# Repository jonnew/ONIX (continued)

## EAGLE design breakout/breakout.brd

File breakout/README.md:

:warning: This project has moved to a dedicated repository: https://github.com/open-ephys/onix-breakout
This folder should be considered archived.

# ONIX Breakout Board
This board allows bench access to the IO provided by the
[fmc-host board](../fmc-host/README.md). It features:

- 4x headstage ports, each with a power switch
- 3x, passive, high-seed clock feed throughs
- BNC, IDC (ribbon), or direct wire access to 12 analog inputs or outputs
- IDC (ribbon) or direct wire access to 8 digital outputs and 8 digital inpouts
- 6 buttons for marking experimental events
- 41 state-indication LEDs
- Full-speed, USB 2.0 access to the onboard [TinyFPGA
  BX](https://www.crowdsupply.com/tinyfpga/tinyfpga-bx) for communication,
  programming, and customization 
- HARP bus
- Rugged M6 or 1/4-20 mounting options compliant with 19" racks and optical
  tables
- Fully open-source gateware and use of fully open-source FPGA toolchain (yosys
  & nextpnr)

## Documentation
Documentation can be found
[here](https://open-ephys.github.io/onix-docs/Hardware%20Guide/Breakout%20Boards/breakout_1r4.html)

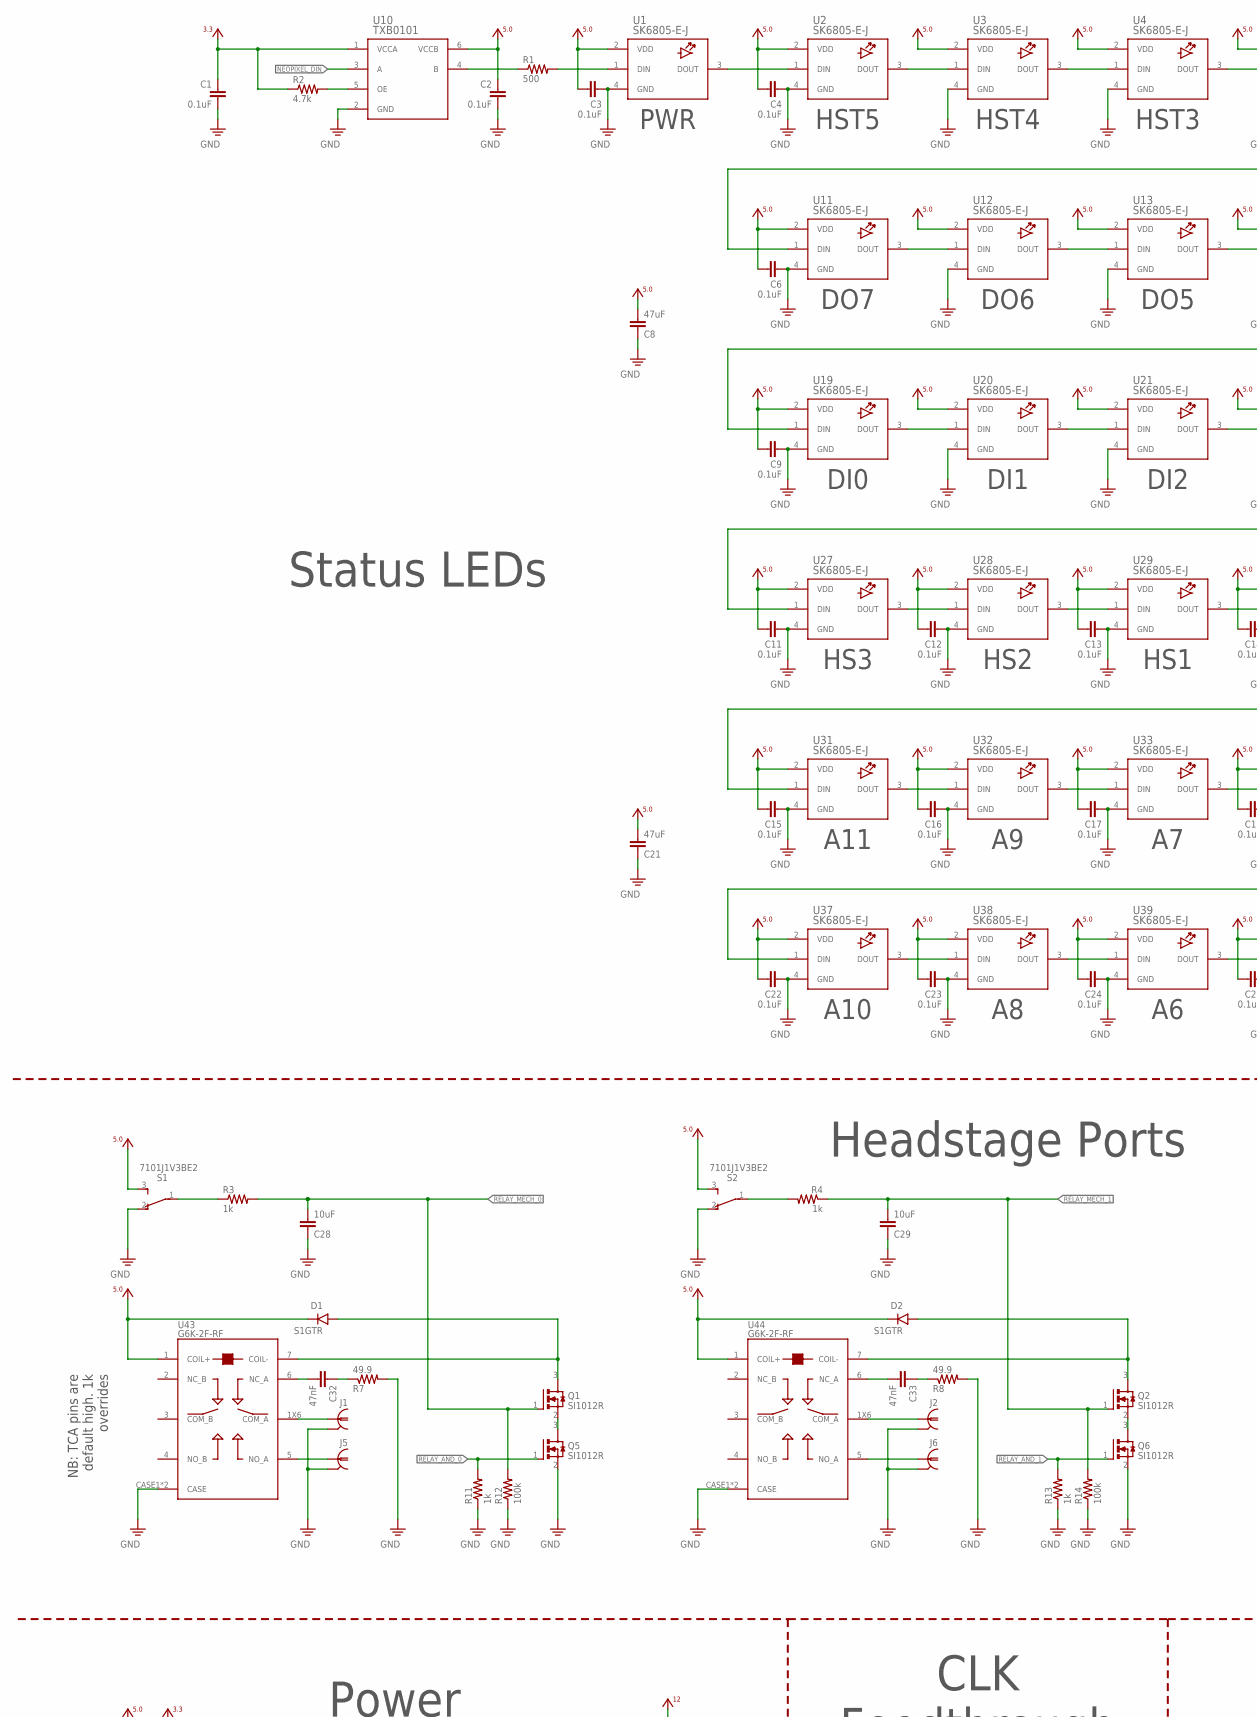
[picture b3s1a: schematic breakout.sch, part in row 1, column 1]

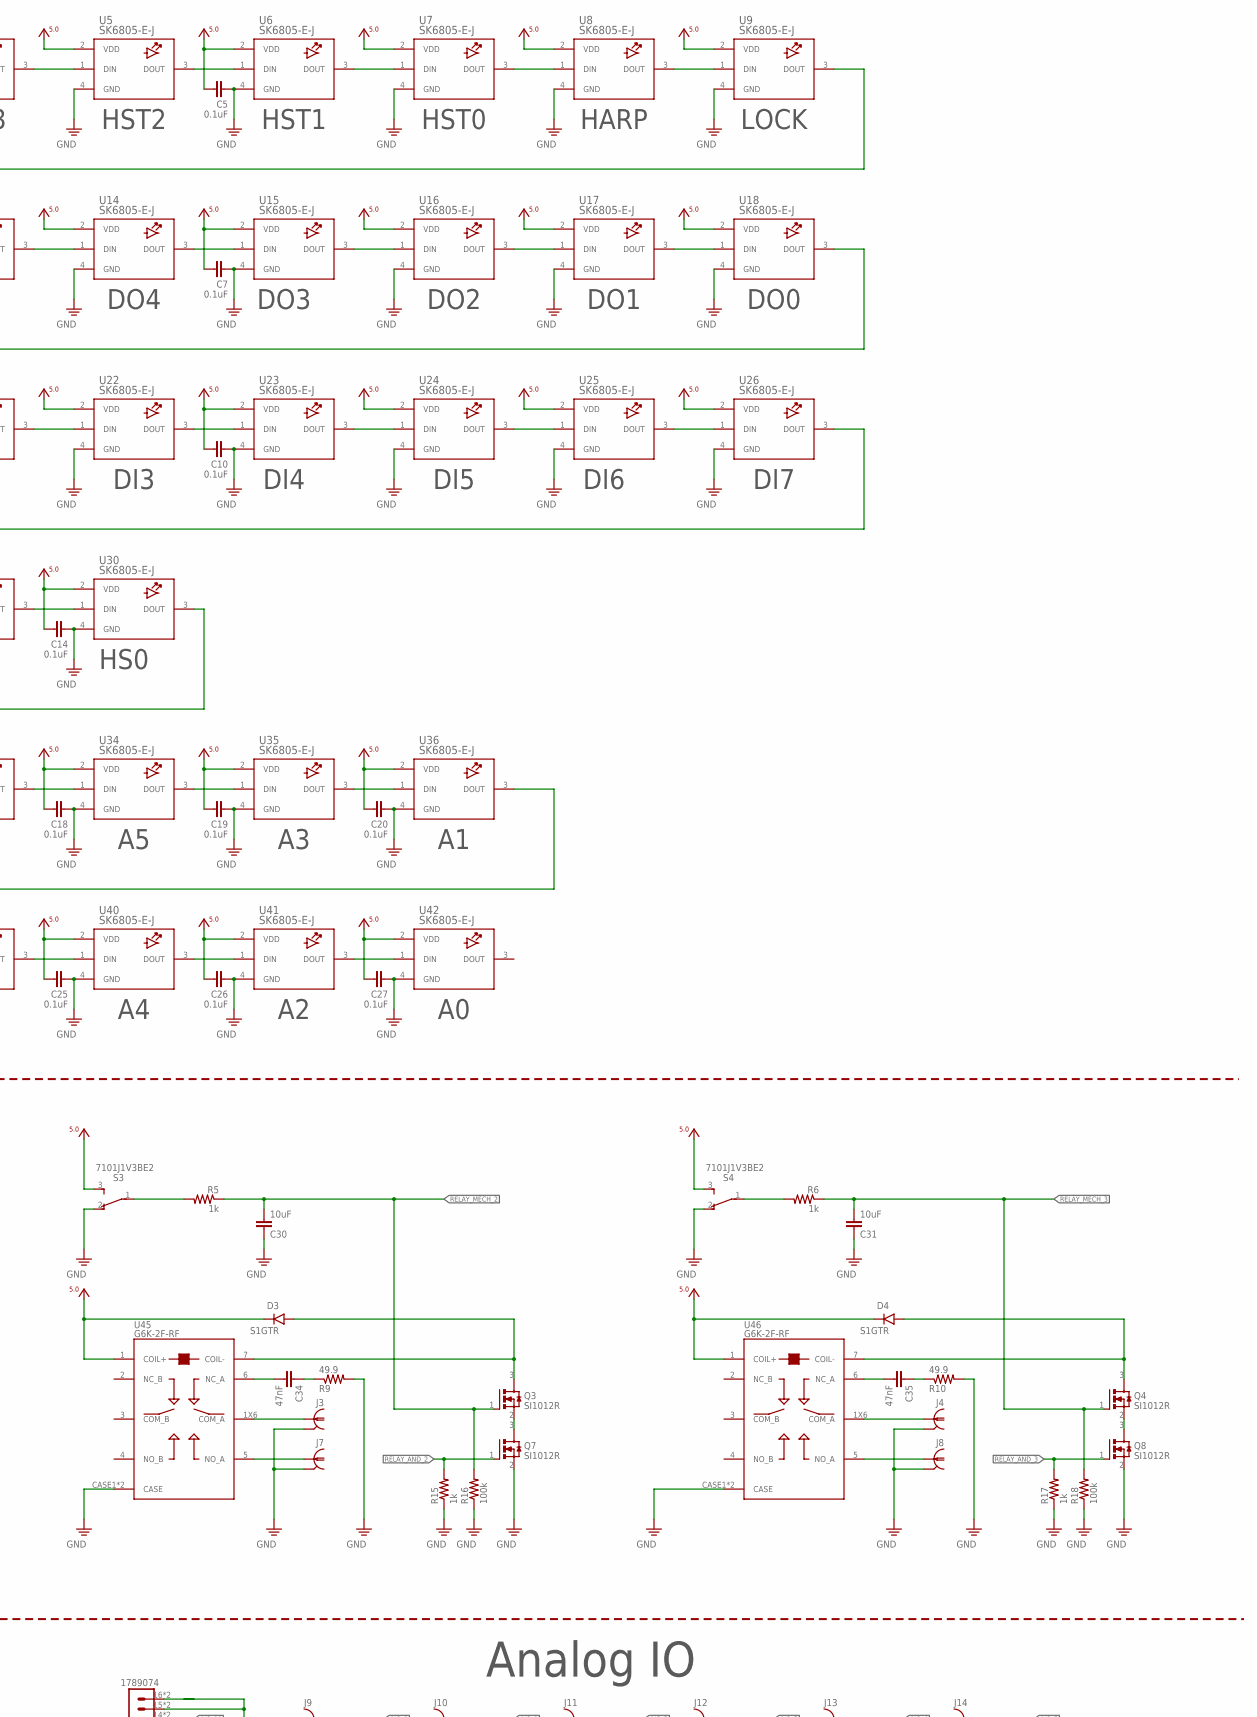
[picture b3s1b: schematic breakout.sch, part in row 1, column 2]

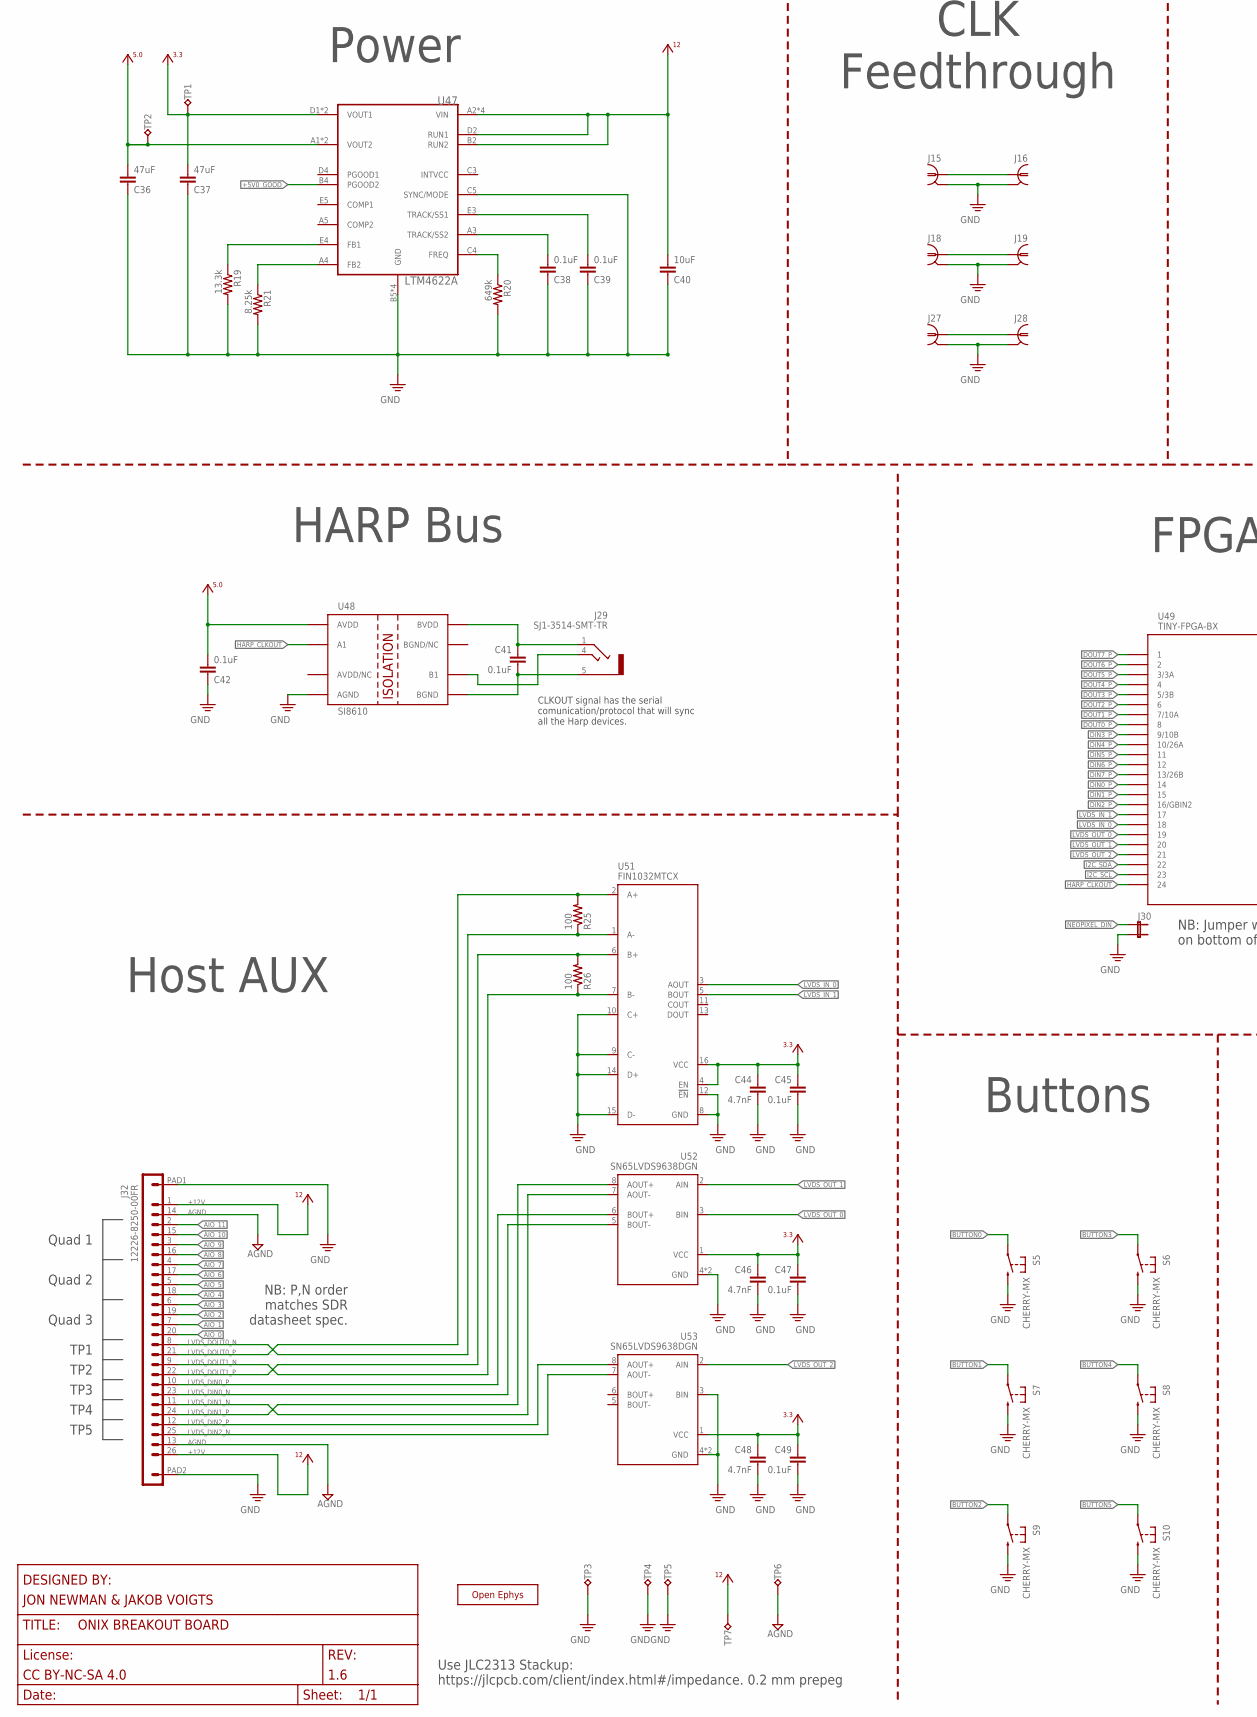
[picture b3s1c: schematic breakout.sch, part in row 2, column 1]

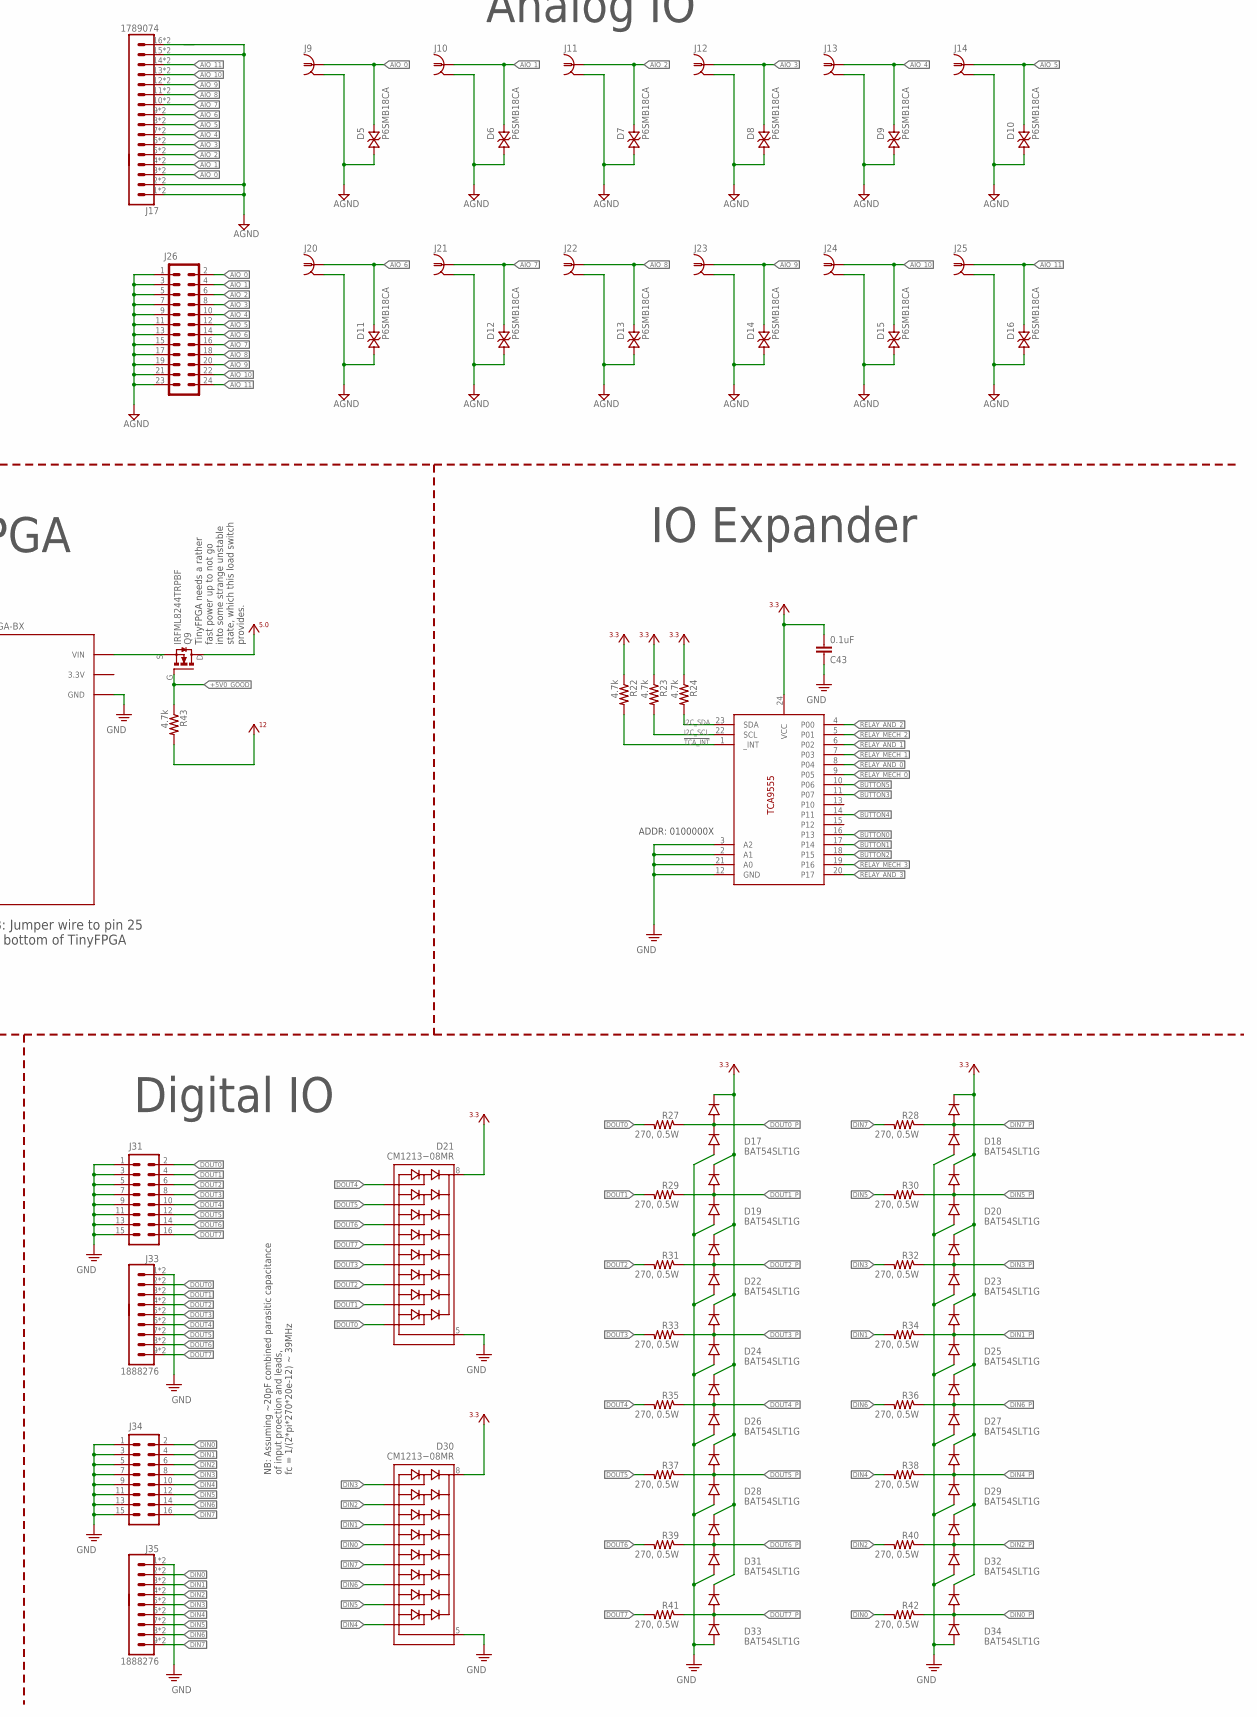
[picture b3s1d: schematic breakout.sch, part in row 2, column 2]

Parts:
C1, C2, C3, C4, C5, C6, C7, C9, C10, C11, C12, C13, C14, C15, C16, C17, C18, C19, C20, C22, C23, C24, C25, C26, C27, C38, C39, C41, C42, C43, C45, C47, C49: 0.1uF; 0402
C8, C21, C36, C37: 47uF; 1210
C28, C29, C30, C31, C40: 10uF; 0805
C32, C33, C34, C35: 47nF; 0402
C44, C46, C48: 4.7nF; 0402
D1, D2, D3, D4: S1GTR; SMA-DO214AC
D5, D6, D7, D8, D9, D10, D11, D12, D13, D14, D15, D16: P6SMB18CA; SMA-DO214AC
D17, D18, D19, D20, D22, D23, D24, D25, D26, D27, D28, D29, D31, D32, D33, D34: BAT54SLT1G; SOT23
D21, D30: CM1213−08MR; MSOP-10-3X3
J1, J2, J3, J4, J16, J19, J28: COAX_SMA-VERT; SMA_JACK_142-0701-201
J5, J6, J7, J8, J15, J18, J27: COAX_MMCX-THRU; MMCX-THRU
J9, J10, J11, J12, J13, J14, J20, J21, J22, J23, J24, J25: COAX_0731010360; 0731010360
J17: 1789074; SCREW16-2
J26: 69168-124HLF; 2X12-BIG
J29: SJ1-3514-SMT-TR; 35RASMT2BHNTRX
J30: JP2E_THRU-HOLE; JP2
J31, J34: 69168-116HLF; 2X08-BIG
J32: 12226-8250-00FR; 12226-82X0-00XX
J33, J35: 1888276; SCREW9-2
Q1, Q2, Q3, Q4, Q5, Q6, Q7, Q8: SI1012R; SC75
Q9: IRFML8244TRPBF; SOT23-GSD
R1: 500; 0402
R2, R22, R23, R24, R43: 4.7k; 0402
R3, R4, R5, R6, R11, R13, R15, R17: 1k; 0402
R7, R8, R9, R10: 49.9; 0402
R12, R14, R16, R18: 100k; 0402
R19: 13.3k; 0402
R20: 649k; 0402
R21: 8.25k; 0402
R25, R26: 100; 0402
R27, R28, R29, R30, R31, R32, R33, R34, R35, R36, R37, R38, R39, R40, R41, R42: 270, 0.5W; 0805
S1, S2, S3, S4: 7101J1V3BE2; CK_7101J1V3QE2
S5, S6, S7, S8, S9, S10: CHERRY-MX
TP1, TP2: TPTP19R; TP19R
TP3, TP4, TP5, TP6, TP7: TP_2MM; TESTPOINT_2MM
U1, U2, U3, U4, U5, U6, U7, U8, U9, U11, U12, U13, U14, U15, U16, U17, U18, U19, U20, U21, U22, U23, U24, U25, U26, U27, U28, U29, U30, U31, U32, U33, U34, U35, U36, U37, U38, U39, U40, U41, U42: SK6805-E-J; NEOPIXEL-1.5X1.5
U10: TXB0101; SOT23-6
U43, U44, U45, U46: G6K-2F-RF; G6KU-2F-RF
U47: LTM4622A; BGA_5X5_625X625
U48: SI8610; SO-08
U49: TINY-FPGA-BX; TINY-FPGA-BX_BASIC
U50: TCA9555; TSSOP-24
U51: FIN1032MTCX; TSSOP-16
U52, U53: SN65LVDS9638DGN; MSOP-8-PAD-3X3
X: OE-LOGO_28X20; OE-LOGO-28X20

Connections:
!TCA_INT: R22.2, U50.1 (_INT)
+3V3: C1.1, C37.2, C43.2, C44.1, C45.1, C46.1, C47.1, C48.1, C49.1, D17.2 (C), D18.2 (C), D19.2 (C), D20.2 (C), D21.8 (VCC), D22.2 (C), D23.2 (C), D24.2 (C), D25.2 (C), D26.2 (C), D27.2 (C), D28.2 (C), D29.2 (C), D30.8 (VCC), D31.2 (C), D32.2 (C), D33.2 (C), D34.2 (C), R2.1, R22.1, R23.1, R24.1, TP1.TP, U10.1 (VCCA), U47.D1 (VOUT1), U47.E1 (VOUT1), U50.24 (VCC), U51.4 (EN), U51.16 (VCC), U52.1 (VCC), U53.1 (VCC)
+5V0: C2.1, C3.2, C4.2, C5.2, C6.2, C7.2, C8.2, C9.2, C10.2, C11.2, C12.2, C13.2, C14.2, C15.2, C16.2, C17.2, C18.2, C19.2, C20.2, C21.2, C22.2, C23.2, C24.2, C25.2, C26.2, C27.2, C36.2, C42.2, D1.C, D2.C, D3.C, D4.C, Q9.D, S1.3, S2.3, S3.3, S4.3, TP2.TP, U1.2 (VDD), U2.2 (VDD), U3.2 (VDD), U4.2 (VDD), U5.2 (VDD), U6.2 (VDD), U7.2 (VDD), U8.2 (VDD), U9.2 (VDD), U10.6 (VCCB), U11.2 (VDD), U12.2 (VDD), U13.2 (VDD), U14.2 (VDD), U15.2 (VDD), U16.2 (VDD), U17.2 (VDD), U18.2 (VDD), U19.2 (VDD), U20.2 (VDD), U21.2 (VDD), U22.2 (VDD), U23.2 (VDD), U24.2 (VDD), U25.2 (VDD), U26.2 (VDD), U27.2 (VDD), U28.2 (VDD), U29.2 (VDD), U30.2 (VDD), U31.2 (VDD), U32.2 (VDD), U33.2 (VDD), U34.2 (VDD), U35.2 (VDD), U36.2 (VDD), U37.2 (VDD), U38.2 (VDD), U39.2 (VDD), U40.2 (VDD), U41.2 (VDD), U42.2 (VDD), U43.1 (COIL+), U44.1 (COIL+), U45.1 (COIL+), U46.1 (COIL+), U47.A1 (VOUT2), U47.B1 (VOUT2), U48.1 (AVDD)
+5V0_GOOD: Q9.G, R43.1, U47.B4 (PGOOD2)
+12V: C40.2, J32.1, J32.26, R43.2, TP7.1, U47.A2 (VIN), U47.B2 (RUN2), U47.B3 (VIN), U47.D2 (RUN1), U47.D3 (VIN), U47.E2 (VIN)
AGND: D5.A (1), D6.A (1), D7.A (1), D8.A (1), D9.A (1), D10.A (1), D11.A (1), D12.A (1), D13.A (1), D14.A (1), D15.A (1), D16.A (1), J9.2, J9.3 (2), J9.4 (2), J9.5 (2), J10.2, J10.3 (2), J10.4 (2), J10.5 (2), J11.2, J11.3 (2), J11.4 (2), J11.5 (2), J12.2, J12.3 (2), J12.4 (2), J12.5 (2), J13.2, J13.3 (2), J13.4 (2), J13.5 (2), J14.2, J14.3 (2), J14.4 (2), J14.5 (2), J17.1, J17.2, J17.15, J17.16, J17.17 (1), J17.18 (2), J17.31 (15), J17.32 (16), J20.2, J20.3 (2), J20.4 (2), J20.5 (2), J21.2, J21.3 (2), J21.4 (2), J21.5 (2), J22.2, J22.3 (2), J22.4 (2), J22.5 (2), J23.2, J23.3 (2), J23.4 (2), J23.5 (2), J24.2, J24.3 (2), J24.4 (2), J24.5 (2), J25.2, J25.3 (2), J25.4 (2), J25.5 (2), J26.1, J26.3, J26.5, J26.7, J26.9, J26.11, J26.13, J26.15, J26.17, J26.19, J26.21, J26.23, J32.13, J32.14, TP6.1
AIO_0: D5.C (2), J9.1, J17.3, J17.19 (3), J26.2, J32.20
AIO_1: D6.C (2), J10.1, J17.4, J17.20 (4), J26.4, J32.7
AIO_2: D7.C (2), J11.1, J17.5, J17.21 (5), J26.6, J32.19
AIO_3: D8.C (2), J12.1, J17.6, J17.22 (6), J26.8, J32.6
AIO_4: D9.C (2), J13.1, J17.7, J17.23 (7), J26.10, J32.18
AIO_5: D10.C (2), J14.1, J17.8, J17.24 (8), J26.12, J32.5
AIO_6: D11.C (2), J17.9, J17.25 (9), J20.1, J26.14, J32.17
AIO_7: D12.C (2), J17.10, J17.26 (10), J21.1, J26.16, J32.4
AIO_8: D13.C (2), J17.11, J17.27 (11), J22.1, J26.18, J32.16
AIO_9: D14.C (2), J17.12, J17.28 (12), J23.1, J26.20, J32.3
AIO_10: D15.C (2), J17.13, J17.29 (13), J24.1, J26.22, J32.15
AIO_11: D16.C (2), J17.14, J17.30 (14), J25.1, J26.24, J32.2
BUTTON0: S5.SW1, U50.16 (P13)
BUTTON1: S7.SW1, U50.17 (P14)
BUTTON2: S9.SW1, U50.18 (P15)
BUTTON3: S6.SW1, U50.11 (P07)
BUTTON4: S8.SW1, U50.14 (P11)
BUTTON5: S10.SW1, U50.10 (P06)
DIN0: D30.4 (CH4), J34.2, J35.2, J35.11 (2), R42.2
DIN0_P: D34.3 (COMM), R42.1, U49.14
DIN1: D30.3 (CH3), J34.4, J35.3, J35.12 (3), R34.2
DIN1_P: D25.3 (COMM), R34.1, U49.15
DIN2: D30.2 (CH2), J34.6, J35.4, J35.13 (4), R40.2
DIN2_P: D32.3 (COMM), R40.1, U49.16 (16/GBIN2)
DIN3: D30.1 (CH1), J34.8, J35.5, J35.14 (5), R32.2
DIN3_P: D23.3 (COMM), R32.1, U49.9 (9/10B)
DIN4: D30.10 (CH8), J34.10, J35.6, J35.15 (6), R38.2
DIN4_P: D29.3 (COMM), R38.1, U49.10 (10/26A)
DIN5: D30.9 (CH7), J34.12, J35.7, J35.16 (7), R30.2
DIN5_P: D20.3 (COMM), R30.1, U49.11
DIN6: D30.7 (CH6), J34.14, J35.8, J35.17 (8), R36.2
DIN6_P: D27.3 (COMM), R36.1, U49.12
DIN7: D30.6 (CH5), J34.16, J35.9, J35.18 (9), R28.2
DIN7_P: D18.3 (COMM), R28.1, U49.13 (13/26B)
DOUT0: D21.10 (CH8), J31.2, J33.2, J33.11 (2), R27.2
DOUT0_P: D17.3 (COMM), R27.1, U49.8
DOUT1: D21.9 (CH7), J31.4, J33.3, J33.12 (3), R29.2
DOUT1_P: D19.3 (COMM), R29.1, U49.7 (7/10A)
DOUT2: D21.7 (CH6), J31.6, J33.4, J33.13 (4), R31.2
DOUT2_P: D22.3 (COMM), R31.1, U49.6
DOUT3: D21.6 (CH5), J31.8, J33.5, J33.14 (5), R33.2
DOUT3_P: D24.3 (COMM), R33.1, U49.5 (5/3B)
DOUT4: D21.1 (CH1), J31.10, J33.6, J33.15 (6), R35.2
DOUT4_P: D26.3 (COMM), R35.1, U49.4
DOUT5: D21.2 (CH2), J31.12, J33.7, J33.16 (7), R37.2
DOUT5_P: D28.3 (COMM), R37.1, U49.3 (3/3A)
DOUT6: D21.3 (CH3), J31.14, J33.8, J33.17 (8), R39.2
DOUT6_P: D31.3 (COMM), R39.1, U49.2
DOUT7: D21.4 (CH4), J31.16, J33.9, J33.18 (9), R41.2
DOUT7_P: D33.3 (COMM), R41.1, U49.1
GND: C1.2, C2.2, C3.1, C4.1, C5.1, C6.1, C7.1, C8.1, C9.1, C10.1, C11.1, C12.1, C13.1, C14.1, C15.1, C16.1, C17.1, C18.1, C19.1, C20.1, C21.1, C22.1, C23.1, C24.1, C25.1, C26.1, C27.1, C28.1, C29.1, C30.1, C31.1, C36.1, C37.1, C38.1, C39.1, C40.1, C42.1, C43.1, C44.2, C45.2, C46.2, C47.2, C48.2, C49.2, D17.1 (A), D18.1 (A), D19.1 (A), D20.1 (A), D21.5 (VSS), D22.1 (A), D23.1 (A), D24.1 (A), D25.1 (A), D26.1 (A), D27.1 (A), D28.1 (A), D29.1 (A), D30.5 (VSS), D31.1 (A), D32.1 (A), D33.1 (A), D34.1 (A), J1.GND$1 (2), J1.GND$2 (2), J1.GND$3 (2), J1.GND$4 (2), J2.GND$1 (2), J2.GND$2 (2), J2.GND$3 (2), J2.GND$4 (2), J3.GND$1 (2), J3.GND$2 (2), J3.GND$3 (2), J3.GND$4 (2), J4.GND$1 (2), J4.GND$2 (2), J4.GND$3 (2), J4.GND$4 (2), J5.GND@1 (2), J5.GND@2 (2), J5.GND@3 (2), J5.GND@4 (2), J6.GND@1 (2), J6.GND@2 (2), J6.GND@3 (2), J6.GND@4 (2), J7.GND@1 (2), J7.GND@2 (2), J7.GND@3 (2), J7.GND@4 (2), J8.GND@1 (2), J8.GND@2 (2), J8.GND@3 (2), J8.GND@4 (2), J15.GND@1 (2), J15.GND@2 (2), J15.GND@3 (2), J15.GND@4 (2), J16.GND$1 (2), J16.GND$2 (2), J16.GND$3 (2), J16.GND$4 (2), J18.GND@1 (2), J18.GND@2 (2), J18.GND@3 (2), J18.GND@4 (2), J19.GND$1 (2), J19.GND$2 (2), J19.GND$3 (2), J19.GND$4 (2), J27.GND@1 (2), J27.GND@2 (2), J27.GND@3 (2), J27.GND@4 (2), J28.GND$1 (2), J28.GND$2 (2), J28.GND$3 (2), J28.GND$4 (2), J30.2, J31.1, J31.3, J31.5, J31.7, J31.9, J31.11, J31.13, J31.15, J32.PAD1, J32.PAD2, J33.1, J33.10 (1), J34.1, J34.3, J34.5, J34.7, J34.9, J34.11, J34.13, J34.15, J35.1, J35.10 (1), Q5.2 (S), Q6.2 (S), Q7.2 (S), Q8.2 (S), R7.2, R8.2, R9.2, R10.2, R11.1, R12.1, R13.1, R14.1, R15.1, R16.1, R17.1, R18.1, R19.2, R20.2, R21.2, S1.2 (1), S2.2 (1), S3.2 (1), S4.2 (1), S5.SW2 (S), S6.SW2 (S), S7.SW2 (S), S8.SW2 (S), S9.SW2 (S), S10.SW2 (S), TP3.1, TP4.1, TP5.1, U1.4 (GND), U2.4 (GND), U3.4 (GND), U4.4 (GND), U5.4 (GND), U6.4 (GND), U7.4 (GND), U8.4 (GND), U9.4 (GND), U10.2 (GND), U11.4 (GND), U12.4 (GND), U13.4 (GND), U14.4 (GND), U15.4 (GND), U16.4 (GND), U17.4 (GND), U18.4 (GND), U19.4 (GND), U20.4 (GND), U21.4 (GND), U22.4 (GND), U23.4 (GND), U24.4 (GND), U25.4 (GND), U26.4 (GND), U27.4 (GND), U28.4 (GND), U29.4 (GND), U30.4 (GND), U31.4 (GND), U32.4 (GND), U33.4 (GND), U34.4 (GND), U35.4 (GND), U36.4 (GND), U37.4 (GND), U38.4 (GND), U39.4 (GND), U40.4 (GND), U41.4 (GND), U42.4 (GND), U43.CASE1 (CASE), U43.CASE2 (CASE), U44.CASE1 (CASE), U44.CASE2 (CASE), U45.CASE1 (CASE), U45.CASE2 (CASE), U46.CASE1 (CASE), U46.CASE2 (CASE), U47.B5 (GND), U47.C1 (GND), U47.C2 (GND), U47.C5 (SYNC/MODE), U47.D5 (GND), U48.4 (AGND), U49.GND@1 (GND), U49.GND@2 (GND), U50.2 (A1), U50.3 (A2), U50.12 (GND), U50.21 (A0), U51.8 (GND), U51.9 (C-), U51.10 (C+), U51.12 (!EN), U51.14 (D+), U51.15 (D-), U52.4 (GND), U52.PAD (GND), U53.3 (BIN), U53.4 (GND), U53.PAD (GND)
HARP_CLKOUT: U48.2 (A1), U49.24
I2C_SCL: R23.2, U49.23, U50.22 (SCL)
I2C_SDA: R24.2, U49.22, U50.23 (SDA)
LOCKED: U9.3 (DOUT), U11.1 (DIN)
LVDS_DIN0_N: J32.23, U52.5 (BOUT-)
LVDS_DIN0_P: J32.10, U52.6 (BOUT+)
LVDS_DIN1_N: J32.11, U52.7 (AOUT-)
LVDS_DIN1_P: J32.24, U52.8 (AOUT+)
LVDS_DIN2_N: J32.25, U53.7 (AOUT-)
LVDS_DIN2_P: J32.12, U53.8 (AOUT+)
LVDS_DOUT0_N: J32.8, R25.1, U51.1 (A-)
LVDS_DOUT0_P: J32.21, R25.2, U51.2 (A+)
LVDS_DOUT1_N: J32.9, R26.1, U51.7 (B-)
LVDS_DOUT1_P: J32.22, R26.2, U51.6 (B+)
LVDS_IN_0: U49.18, U51.3 (AOUT)
LVDS_IN_1: U49.17, U51.5 (BOUT)
LVDS_OUT_0: U49.19, U52.3 (BIN)
LVDS_OUT_1: U49.20, U52.2 (AIN)
LVDS_OUT_2: U49.21, U53.2 (AIN)
unnamed: J15.SIG (1), J16.CLK (1)
unnamed: J18.SIG (1), J19.CLK (1)
unnamed: J27.SIG (1), J28.CLK (1)
unnamed: D1.A, Q1.3 (D), U43.7 (COIL-)
unnamed: Q1.2 (S), Q5.3 (D)
unnamed: U11.3 (DOUT), U12.1 (DIN)
unnamed: U12.3 (DOUT), U13.1 (DIN)
unnamed: U13.3 (DOUT), U14.1 (DIN)
unnamed: U36.3 (DOUT), U37.1 (DIN)
unnamed: U31.3 (DOUT), U32.1 (DIN)
unnamed: D2.A, Q2.3 (D), U44.7 (COIL-)
unnamed: U15.3 (DOUT), U16.1 (DIN)
unnamed: U16.3 (DOUT), U17.1 (DIN)
unnamed: C32.2, U43.6 (NC_A)
unnamed: C41.1, J29.1, U48.8 (BVDD)
unnamed: C41.2, J29.5, U48.5 (BGND)
unnamed: J29.4, U48.6 (B1)
unnamed: J6.SIG (1), U44.5 (NO_A)
unnamed: U17.3 (DOUT), U18.1 (DIN)
unnamed: U1.3 (DOUT), U2.1 (DIN)
unnamed: C33.1, R8.1
unnamed: R3.1, S1.1 (2)
unnamed: R21.1, U47.A4 (FB2)
unnamed: R19.1, U47.E4 (FB1)
unnamed: C38.2, U47.A3 (TRACK/SS2)
unnamed: C39.2, U47.E3 (TRACK/SS1)
unnamed: J5.SIG (1), U43.5 (NO_A)
unnamed: J1.CLK (1), U43.1X6 (COM_A)
unnamed: C32.1, R7.1
unnamed: C33.2, U44.6 (NC_A)
unnamed: Q3.2 (S), Q7.3 (D)
unnamed: C34.1, R9.1
unnamed: J2.CLK (1), U44.1X6 (COM_A)
unnamed: R4.2, S2.1 (2)
unnamed: C34.2, U45.6 (NC_A)
unnamed: J7.SIG (1), U45.5 (NO_A)
unnamed: R5.2, S3.1 (2)
unnamed: Q2.2 (S), Q6.3 (D)
unnamed: U2.3 (DOUT), U3.1 (DIN)
unnamed: U3.3 (DOUT), U4.1 (DIN)
unnamed: J3.CLK (1), U45.1X6 (COM_A)
unnamed: R6.2, S4.1 (2)
unnamed: C35.1, R10.1
unnamed: C35.2, U46.6 (NC_A)
unnamed: J8.SIG (1), U46.5 (NO_A)
unnamed: J4.CLK (1), U46.1X6 (COM_A)
unnamed: U4.3 (DOUT), U5.1 (DIN)
unnamed: D3.A, Q3.3 (D), U45.7 (COIL-)
unnamed: U6.3 (DOUT), U7.1 (DIN)
unnamed: U7.3 (DOUT), U8.1 (DIN)
unnamed: U8.3 (DOUT), U9.1 (DIN)
unnamed: R1.2, U1.1 (DIN)
unnamed: R1.1, U10.4 (B)
unnamed: U5.3 (DOUT), U6.1 (DIN)
unnamed: R2.2, U10.5 (OE)
unnamed: U14.3 (DOUT), U15.1 (DIN)
unnamed: D4.A, Q4.3 (D), U46.7 (COIL-)
unnamed: Q4.2 (S), Q8.3 (D)
unnamed: Q9.S, U49.VIN
unnamed: U32.3 (DOUT), U33.1 (DIN)
unnamed: U33.3 (DOUT), U34.1 (DIN)
unnamed: U34.3 (DOUT), U35.1 (DIN)
unnamed: U35.3 (DOUT), U36.1 (DIN)
unnamed: U37.3 (DOUT), U38.1 (DIN)
unnamed: U38.3 (DOUT), U39.1 (DIN)
unnamed: U39.3 (DOUT), U40.1 (DIN)
unnamed: U40.3 (DOUT), U41.1 (DIN)
unnamed: U41.3 (DOUT), U42.1 (DIN)
unnamed: U18.3 (DOUT), U19.1 (DIN)
unnamed: U19.3 (DOUT), U20.1 (DIN)
unnamed: U20.3 (DOUT), U21.1 (DIN)
unnamed: U21.3 (DOUT), U22.1 (DIN)
unnamed: U22.3 (DOUT), U23.1 (DIN)
unnamed: U23.3 (DOUT), U24.1 (DIN)
unnamed: U24.3 (DOUT), U25.1 (DIN)
unnamed: U25.3 (DOUT), U26.1 (DIN)
unnamed: U26.3 (DOUT), U27.1 (DIN)
unnamed: U27.3 (DOUT), U28.1 (DIN)
unnamed: U28.3 (DOUT), U29.1 (DIN)
unnamed: U29.3 (DOUT), U30.1 (DIN)
unnamed: U30.3 (DOUT), U31.1 (DIN)
unnamed: R20.1, U47.C4 (FREQ)
NEOPIXEL_DIN: J30.1, U10.3 (A)
RELAY_AND_0: Q5.1 (G), R11.2, U50.8 (P04)
RELAY_AND_1: Q6.1 (G), R13.2, U50.6 (P02)
RELAY_AND_2: Q7.1 (G), R15.2, U50.4 (P00)
RELAY_AND_3: Q8.1 (G), R17.2, U50.20 (P17)
RELAY_MECH_0: C28.2, Q1.1 (G), R3.2, R12.2, U50.9 (P05)
RELAY_MECH_1: C29.2, Q2.1 (G), R4.1, R14.2, U50.7 (P03)
RELAY_MECH_2: C30.2, Q3.1 (G), R5.1, R16.2, U50.5 (P01)
RELAY_MECH_3: C31.2, Q4.1 (G), R6.1, R18.2, U50.19 (P16)

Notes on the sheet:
Use JLC2313 Stackup: https://jlcpcb.com/client/index.html#/impedance. 0.2 mm prepeg
NB: P,N order matches SDR datasheet spec.
Power
Host AUX
Headstage Ports
Analog IO
CLKOUT signal has the serial comunication/protocol that will sync all the Harp devices.
HARP Bus
CLK Feedthrough
Quad 1
Quad 2
Quad 3
TP1
TP2
TP3
TP4
TP5
IO Expander
Buttons
FPGA
Digital IO
Status LEDs
ADDR: 0100000X
NB: Assuming ~20pF combined parasitic capacitance of input proection and leads, fc = 1/(2*pi*270*20e-12) ~ 39MHz
NB: Jumper wire to pin 25 on bottom of TinyFPGA
PWR
HST0
HARP
LOCK
DO7
DO6
DO5
DO4
DO3
DO2
DO1
DO0
DI0
DI1
DI2

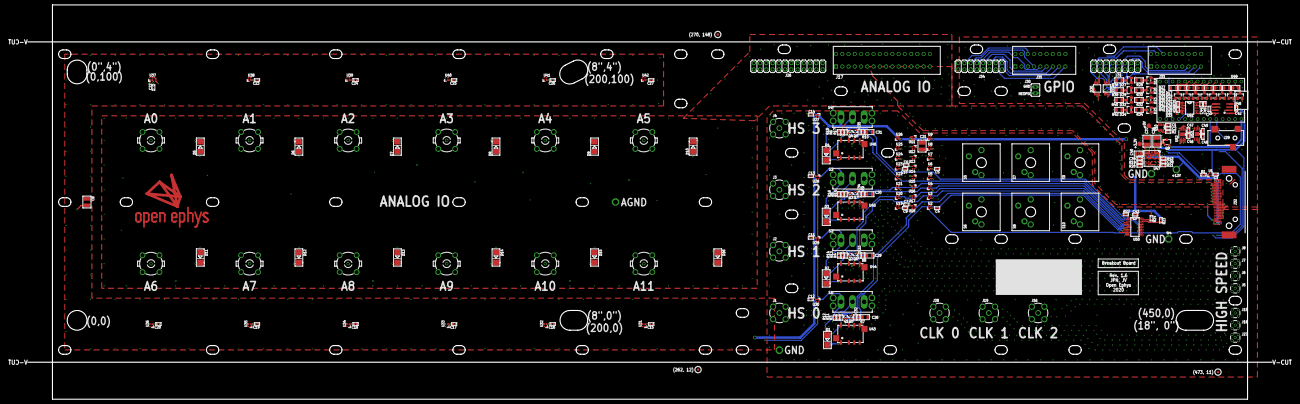
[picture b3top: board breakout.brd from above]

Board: 4 copper layers, 505.0 x 160.0 mm, 244 parts (0 on the bottom side), 167 nets.

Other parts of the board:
E$1, E$3, E$5: FIDUCIAL
